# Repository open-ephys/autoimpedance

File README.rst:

**Warning** This project is deprecated! If you have interest in creating an open source automated electrode plater, please get in touch with us!

=====================
Autoimpedance
=====================

In neuroscience studies, it's important to measure electrode impedances before every experiment. If impedance levels are not in the right range, they must be adjusted by plating electrode tips with gold or platinum. The most common way to do this is with an analog impedance meter and current source, but this method is slow and unreliable. Autoimpedance will be an open-source, digital alternative that aims to speed up the impedance measurement and plating process.

This repository contains code, schematics, and board designs for Autoimpedance. It's based on the Electric Imp and the Analog Devices AD5933_ impedance converter.

Most of the code has been written for Arduino_, but it will soon be translated into Squirrel. PCB layout was done with Eagle_.

What's been done so far
-----------------------------------
- board layout with 32-channel multiplexing capabilities, with the ability to toggle between impedance testing (Analog Devices AD5933) and an adjustable current source (LM234).
- assemble prototype board and verify that multiplexing is working (multiplexing.pde_)
- write code for I2C communication with AD5933 and AD5245 programmable potentiometer (autoimpedance.pde_)

TODO List (short term)
-------------------------------
- calibrate the AD5933 (see instructions in the datasheet_)
- calibrate the LM234 adjustable current source
- create a simple webpage to manually control the device via WiFi
- write and refine a simple feedback algorithm to automatically bring impedance to desired levels
- design and manufacture a case

.. _AD5933: http://www.analog.com/en/rfif-components/direct-digital-synthesis-dds/ad5933/products/product.html
.. _Arduino: http://www.arduino.cc/
.. _Eagle: http://www.cadsoftusa.com/
.. _datasheet: https://github.com/open-ephys/autoimpedance/blob/master/PCB/AD5933.pdf
.. _autoimpedance.pde: https://github.com/open-ephys/autoimpedance/blob/master/autoimpedance.pde
.. _multiplexing.pde: https://github.com/open-ephys/autoimpedance/blob/master/multiplexing.pde

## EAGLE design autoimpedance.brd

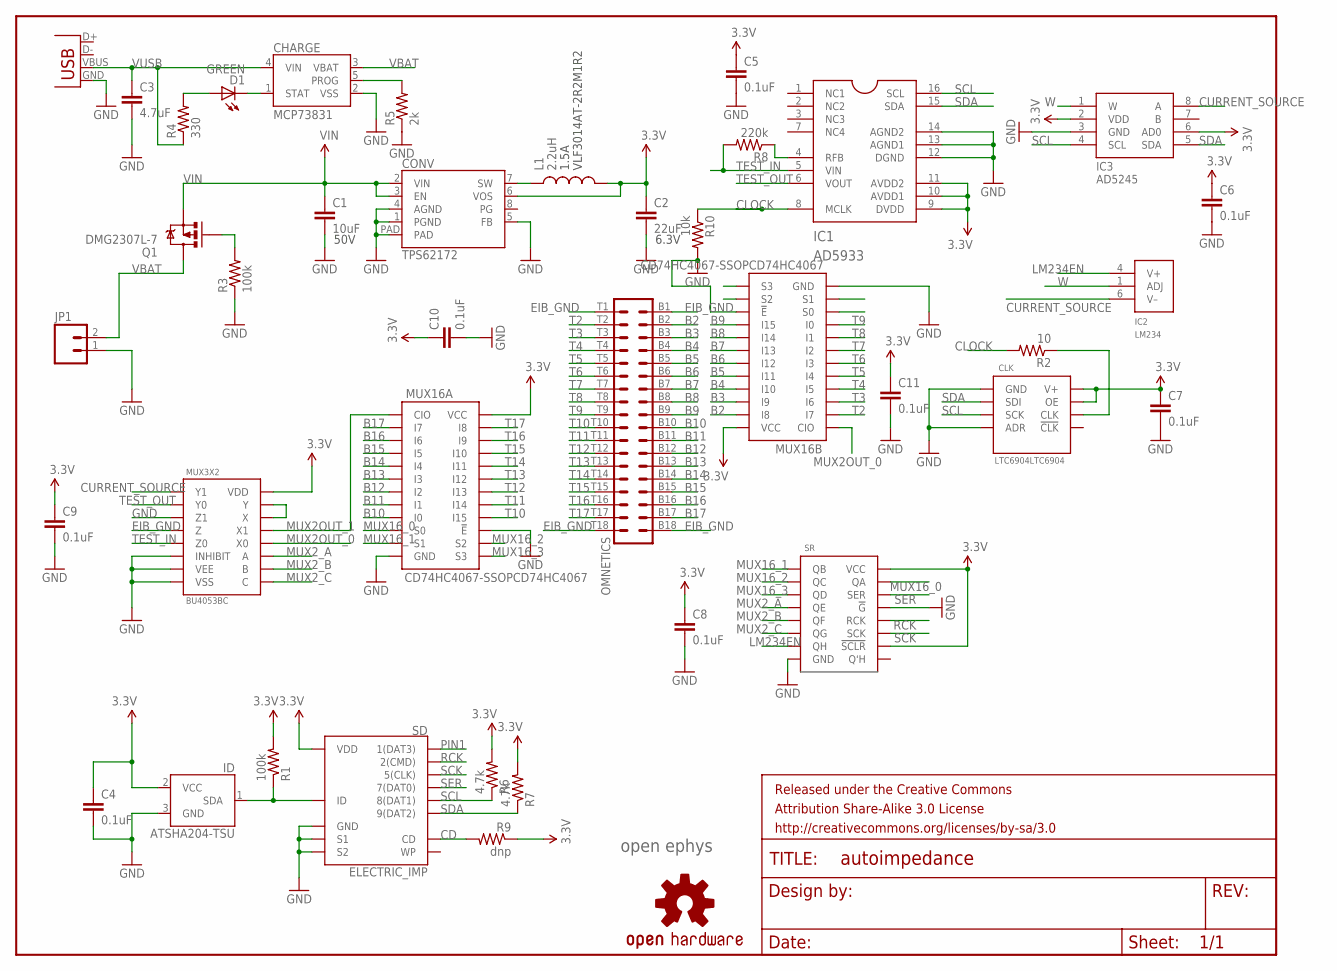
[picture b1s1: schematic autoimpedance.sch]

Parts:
C1: 10uF; 1210
C2: 22uF; 0805
C3: 4.7uF; 1210
C4, C5, C6, C7, C8, C9, C10, C11: 0.1uF; 0603-CAP
CHARGE: MCP73831; SOT23-5
CLK: LTC6904LTC6904; MSOP08
CONV: TPS62172; WSON-8-PAD
D1: GREEN; LED-0603
FRAME1: FRAME-LETTER; CREATIVE_COMMONS
IC1: AD5933
IC2: LM234
IC3: AD5245
ID: ATSHA204-TSU; SOT23-3
JP1: M02SMD; 1X02_SMD
L1: 2.2uH; VLF4012A
MUX3X2: BU4053BC; SSOP16
MUX16A, MUX16B: CD74HC4067-SSOPCD74HC4067; SSOP24
OMNETICS: OMNETICS_A79025
Q1: DMG2307L-7; SOT23-3
R1, R3: 100k; 0402-RES
R2: 10; 0402-RES
R4: 330; 0402-RES
R5: 2k; 0402-RES
R6, R7: 4.7k; 0402-RES
R8: 220k; 0402-RES
R9: dnp; 0402-RES
R10: 10k; 0402-RES
SD: ELECTRIC_IMP; SD_MMC_SOCKET
SR: MM74HC595MM74HC595; TSSOP16
U$5: OSHW-LOGOS; OSHW-LOGO-S
U$7: OPEN_EPHYS_LOGO
USB: USBSMD; USB-MINIB

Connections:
3.3V: C2.1, C4.1, C5.1, C6.1, C7.1, C8.1, C9.1, C10.1, C11.1, CLK.7 (OE), CLK.8 (V+), CONV.6 (VOS), IC1.9 (DVDD), IC1.10 (AVDD1), IC1.11 (AVDD2), IC3.2 (VDD), IC3.6 (AD0), ID.2 (VCC), L1.P$2 (2), MUX3X2.16 (VDD), MUX16A.24 (VCC), MUX16B.24 (VCC), R1.2, R6.2, R7.2, R9.1, SD.4 (VDD), SR.10 (!SCLR), SR.16 (VCC)
B2: MUX16B.23 (I8), OMNETICS.B2
B3: MUX16B.22 (I9), OMNETICS.B3
B4: MUX16B.21 (I10), OMNETICS.B4
B5: MUX16B.20 (I11), OMNETICS.B5
B6: MUX16B.19 (I12), OMNETICS.B6
B7: MUX16B.18 (I13), OMNETICS.B7
B8: MUX16B.17 (I14), OMNETICS.B8
B9: MUX16B.16 (I15), OMNETICS.B9
B10: MUX16A.9 (I0), OMNETICS.B10
B11: MUX16A.8 (I1), OMNETICS.B11
B12: MUX16A.7 (I2), OMNETICS.B12
B13: MUX16A.6 (I3), OMNETICS.B13
B14: MUX16A.5 (I4), OMNETICS.B14
B15: MUX16A.4 (I5), OMNETICS.B15
B16: MUX16A.3 (I6), OMNETICS.B16
B17: MUX16A.2 (I7), OMNETICS.B17
CD: R9.2, SD.CD
CLOCK: IC1.8 (MCLK), R2.2, R10.1
CURRENT_SOURCE: IC2.6 (V–), IC3.8 (A), MUX3X2.1 (Y1)
EIB_GND: MUX3X2.4 (Z), OMNETICS.B1, OMNETICS.B18, OMNETICS.T1, OMNETICS.T18
GND: C1.2, C2.2, C3.2, C4.2, C5.2, C6.2, C7.2, C8.2, C9.2, C10.2, C11.2, CHARGE.2 (VSS), CLK.1 (GND), CLK.4 (ADR), CONV.1 (PGND), CONV.4 (AGND), CONV.5 (FB), CONV.PAD, IC1.12 (DGND), IC1.13 (AGND1), IC1.14 (AGND2), IC3.3 (GND), ID.3 (GND), JP1.1, MUX3X2.3 (Z1), MUX3X2.6 (INHIBIT), MUX3X2.7 (VEE), MUX3X2.8 (VSS), MUX16A.12 (GND), MUX16A.15 (!E), MUX16B.12 (GND), MUX16B.15 (!E), R3.1, R5.1, R10.2, SD.3 (GND), SD.S1, SD.S2, SR.8 (GND), SR.13 (!G), USB.GND
ID: ID.1 (SDA), R1.1, SD.6 (ID)
LM234EN: IC2.4 (V+), SR.7 (QH)
MUX2OUT_0: MUX3X2.12 (X0), MUX16B.1 (CIO)
MUX2OUT_1: MUX3X2.13 (X1), MUX16A.1 (CIO)
MUX2_A: MUX3X2.11 (A), SR.4 (QE)
MUX2_B: MUX3X2.10 (B), SR.5 (QF)
MUX2_C: MUX3X2.9 (C), SR.6 (QG)
MUX16_0: MUX16A.10 (S0), MUX16B.10 (S0), SR.15 (QA)
MUX16_1: MUX16A.11 (S1), MUX16B.11 (S1), SR.1 (QB)
MUX16_2: MUX16A.14 (S2), MUX16B.14 (S2), SR.2 (QC)
MUX16_3: MUX16A.13 (S3), MUX16B.13 (S3), SR.3 (QD)
unnamed: CONV.7 (SW), L1.P$1 (1)
unnamed: Q1.1 (G), R3.2
unnamed: IC1.4 (RFB), R8.1
unnamed: CHARGE.5 (PROG), R5.2
unnamed: D1.A, R4.2
unnamed: CHARGE.1 (STAT), D1.C
unnamed: CLK.6 (CLK), R2.1
unnamed: MUX3X2.14 (X), MUX3X2.15 (Y)
PIN1: SD.1 (1(DAT3))
RCK: SD.2 (2(CMD)), SR.12 (RCK)
SCK: SD.5 (5(CLK)), SR.11 (SCK)
SCL: CLK.3 (SCK), IC1.16 (SCL), IC3.4 (SCL), R6.1, SD.8 (8(DAT1))
SDA: CLK.2 (SDI), IC1.15 (SDA), IC3.5 (SDA), R7.1, SD.9 (9(DAT2))
SER: SD.7 (7(DAT0)), SR.14 (SER)
T2: MUX16B.2 (I7), OMNETICS.T2
T3: MUX16B.3 (I6), OMNETICS.T3
T4: MUX16B.4 (I5), OMNETICS.T4
T5: MUX16B.5 (I4), OMNETICS.T5
T6: MUX16B.6 (I3), OMNETICS.T6
T7: MUX16B.7 (I2), OMNETICS.T7
T8: MUX16B.8 (I1), OMNETICS.T8
T9: MUX16B.9 (I0), OMNETICS.T9
T10: MUX16A.16 (I15), OMNETICS.T10
T11: MUX16A.17 (I14), OMNETICS.T11
T12: MUX16A.18 (I13), OMNETICS.T12
T13: MUX16A.19 (I12), OMNETICS.T13
T14: MUX16A.20 (I11), OMNETICS.T14
T15: MUX16A.21 (I10), OMNETICS.T15
T16: MUX16A.22 (I9), OMNETICS.T16
T17: MUX16A.23 (I8), OMNETICS.T17
TEST_IN: IC1.5 (VIN), MUX3X2.5 (Z0), R8.2
TEST_OUT: IC1.6 (VOUT), MUX3X2.2 (Y0)
VBAT: CHARGE.3 (VBAT), JP1.2, Q1.3 (D)
VIN: C1.1, CONV.2 (VIN), CONV.3 (EN), Q1.2 (S)
VUSB: C3.1, CHARGE.4 (VIN), R4.1, USB.VBUS
W: IC2.1 (ADJ), IC3.1 (W)

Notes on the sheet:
50V
6.3V
1.5A
VLF3014AT-2R2M1R2

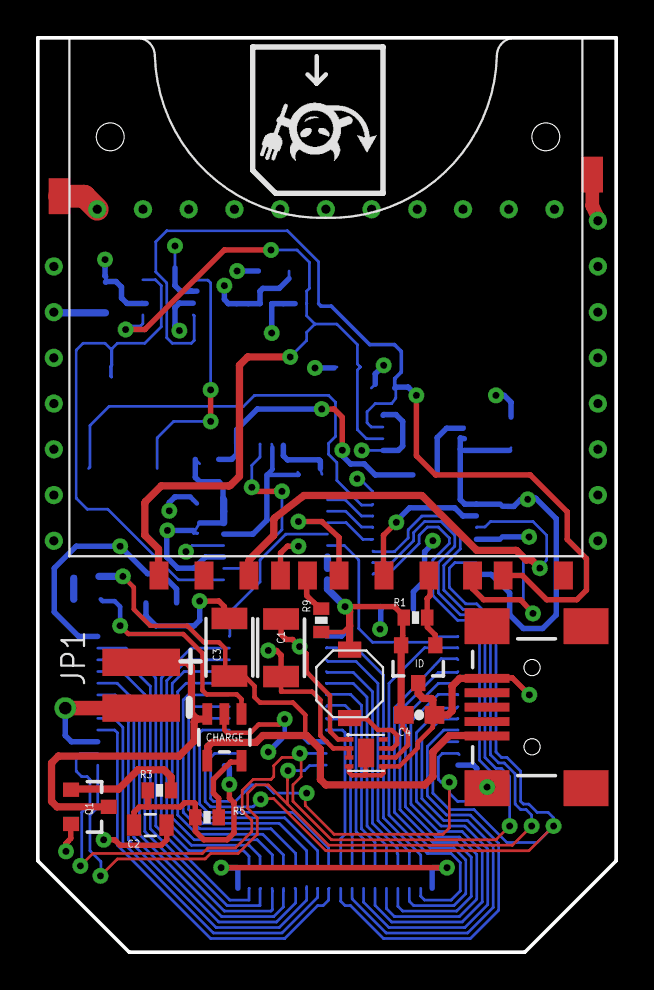
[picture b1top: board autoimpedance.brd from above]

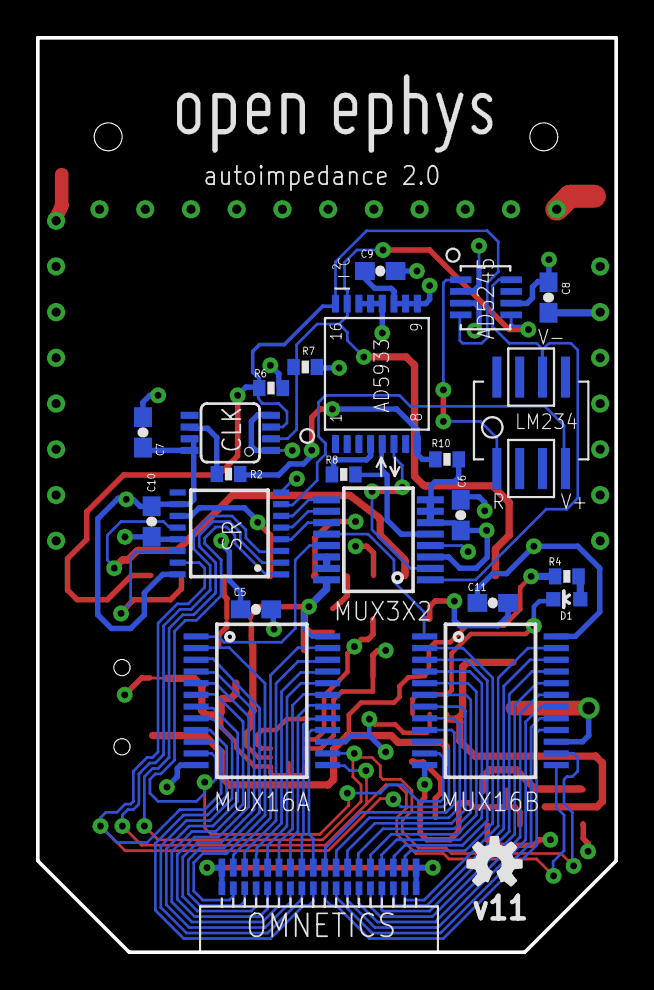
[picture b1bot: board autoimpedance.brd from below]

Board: 4 copper layers, 32.1 x 50.8 mm, 42 parts (25 on the bottom side), 68 nets.

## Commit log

2012-02-11 Initial commit of Autoimpedance code
2012-02-11 Added Eagle files.
2012-03-30 Added additional files
2012-03-30 Changed parts file to plain text
2012-03-30 Moved files into PCB folder
2012-03-30 Added README file
2012-03-30 Edited README file
2012-08-31 Moving files around and renaming
2013-07-23 Update code for new Arduino software
2013-07-23 Add channel selection into serial loop
2013-07-24 Add mux pins to setup()
2013-08-01 Add datasheets folder
2013-08-01 Add new datasheets
2013-08-14 Add electric imp board
2013-08-14 Add electric imp version BOM
2013-08-15 Cleaning up traces
2013-08-21 Fix layout
2013-08-22 Aesthetic fixes
2013-08-22 Fix LM234 channel mapping
2013-08-22 Update BOM
2013-08-22 Rename imp version to autoimpedance
2013-08-22 Remove built for imp logo'
2013-08-22 Add Gerber files and .cam
2013-09-10 Fix incorrect VEE connection on 3x2 MUX
2014-01-02 .pdf & .png images of .sch & .brd files
    For those without Eagle installed
2014-01-06 Switch to i2c89 instead of i2c12
2014-04-06 Started transfering autoimpedance code to the electric imp. Verified that i2c bus works in current hardware revision. Developed functions for changing onboard clock frequency. Started an issues list.
2014-04-07 Programmed control for digital potentiometer.
2014-04-07 Minor.
2014-04-07 Improved the way that resistances and clock frequency are set.
2014-04-07 Changest to allow clock to run at arbitrary frequencies.
2014-04-09 Finished class for controlling shift register.
2014-04-09 Rewrote shift register so it has a smaller footprint. Finished mux class.
2014-04-09 Undo changes to old arduino code.
2014-04-10 Added a bunch of low level functions to the ZSensor object for manipulating the AD5933. These will have to be abstracted up in something more automatic. Not tested yet.
2014-04-12 Functional base driver with control over all chips on the board. Can perform frequency sweeps, measure impedance, etc. Needs to have calibration arthmetic and methods implemented. Added notes about s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
2014-04-12 Implemented plating functionality.
2014-04-12 Noted a strange bug where the requested current seems to be inversely related to the deliverd current. The pots wiper position is the reflection of where it should be.
2014-04-14 Started implementing calibration routines. I am having trouble with the chip -- it does not seem to want to listen to me when I try to reset sweep parameters.
2014-04-16 Fixed a couple issues with the driver code. The calibration routine is still providing rather strange performance. I need a more systematic way of testing this.
2014-05-08 Added a proper channel mapping doc. There is very strange behavior with the device when trying to run an impedance test. Basically, the data registers are always saturated (contain all 0's or 1's). I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
2020-06-02 Deprecate this project

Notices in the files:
parts and their libraries:
SparkFun-RF: Licensing: CC v3.0 Share-Alike You are welcome to use this library for commercial purposes.
SparkFun-Aesthetics: Released under the Creative Commons Attribution Share-Alike 3.0 License
SparkFun-Aesthetics: http://creativecommons.org/licenses/by-sa/3.0
